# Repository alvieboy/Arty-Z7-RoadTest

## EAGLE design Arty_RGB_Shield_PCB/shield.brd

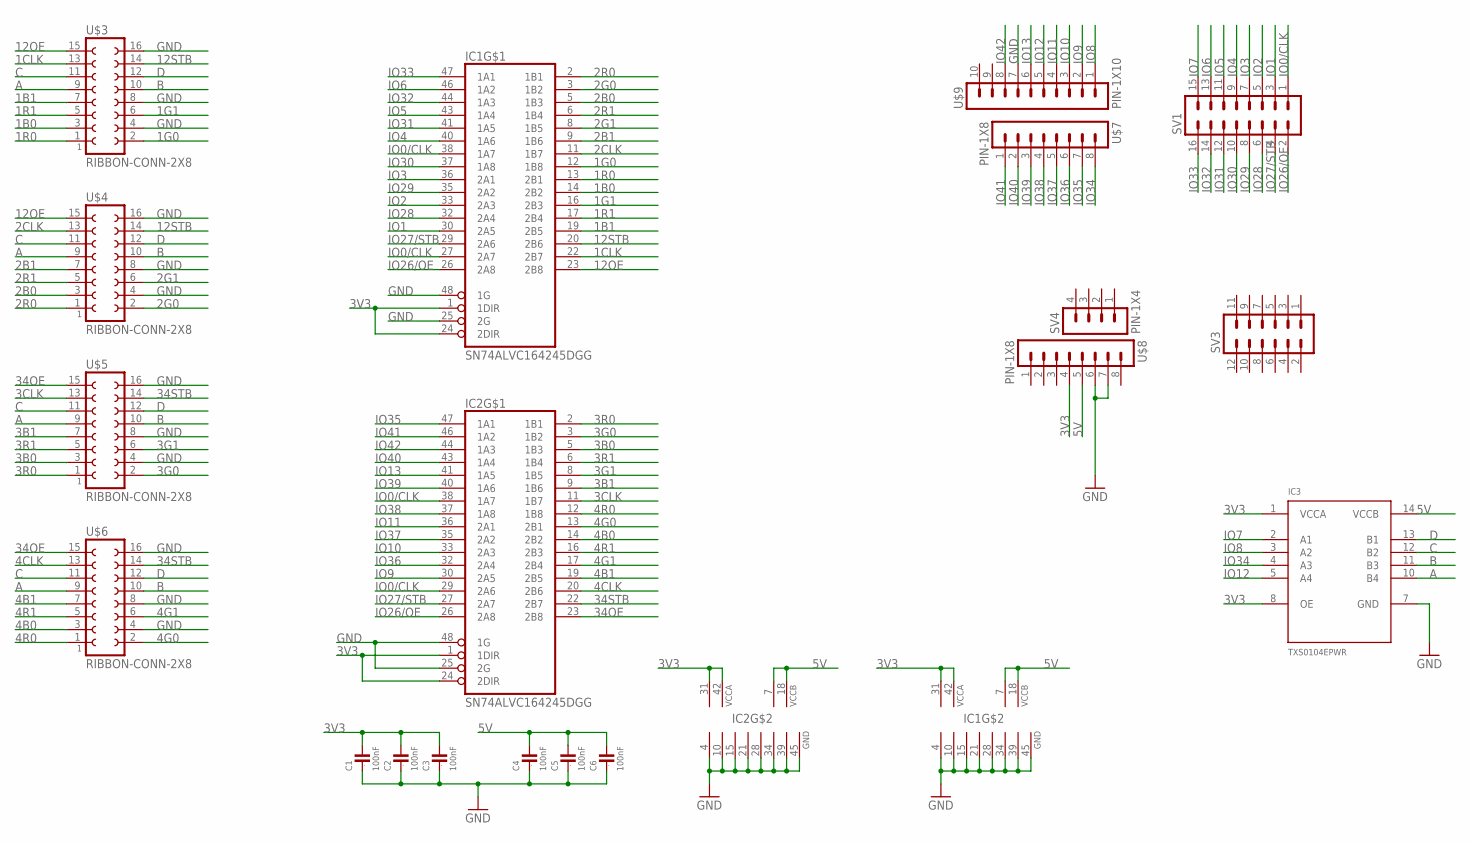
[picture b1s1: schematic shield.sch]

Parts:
C1, C2, C3, C4, C5, C6: 100nF; 0603
IC1, IC2: SN74ALVC164245DGG; TSSOP48
IC3: TXS0104EPWR; TSSOP14
SV1: MA08-2
SV3: MA06-2
SV4: PIN-1X4
U$3, U$4, U$5, U$6: RIBBON-CONN-2X8
U$7, U$8: PIN-1X8
U$9: PIN-1X10

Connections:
1B0: IC1.14 (2B2), U$3.3
1B1: IC1.19 (2B5), U$3.7
1CLK: IC1.22 (2B7), U$3.13
1G0: IC1.12 (1B8), U$3.2
1G1: IC1.16 (2B3), U$3.6
1R0: IC1.13 (2B1), U$3.1
1R1: IC1.17 (2B4), U$3.5
2B0: IC1.5 (1B3), U$4.3
2B1: IC1.9 (1B6), U$4.7
2CLK: IC1.11 (1B7), U$4.13
2G0: IC1.3 (1B2), U$4.2
2G1: IC1.8 (1B5), U$4.6
2R0: IC1.2 (1B1), U$4.1
2R1: IC1.6 (1B4), U$4.5
3B0: IC2.5 (1B3), U$5.3
3B1: IC2.9 (1B6), U$5.7
3CLK: IC2.11 (1B7), U$5.13
3G0: IC2.3 (1B2), U$5.2
3G1: IC2.8 (1B5), U$5.6
3R0: IC2.2 (1B1), U$5.1
3R1: IC2.6 (1B4), U$5.5
3V3: C1.2, C2.2, C3.2, IC1.1 (1DIR), IC1.24 (2DIR), IC1.31 (VCCA), IC1.42 (VCCA), IC2.1 (1DIR), IC2.24 (2DIR), IC2.31 (VCCA), IC2.42 (VCCA), IC3.1 (VCCA), IC3.8 (OE), U$8.4
4B0: IC2.14 (2B2), U$6.3
4B1: IC2.19 (2B5), U$6.7
4CLK: IC2.20 (2B6), U$6.13
4G0: IC2.13 (2B1), U$6.2
4G1: IC2.17 (2B4), U$6.6
4R0: IC2.12 (1B8), U$6.1
4R1: IC2.16 (2B3), U$6.5
5V: C4.2, C5.2, C6.2, IC1.7 (VCCB), IC1.18 (VCCB), IC2.7 (VCCB), IC2.18 (VCCB), IC3.14 (VCCB), U$8.5
12OE: IC1.23 (2B8), U$3.15, U$4.15
12STB: IC1.20 (2B6), U$3.14, U$4.14
34OE: IC2.23 (2B8), U$5.15, U$6.15
34STB: IC2.22 (2B7), U$5.14, U$6.14
A: IC3.10 (B4), U$3.9, U$4.9, U$5.9, U$6.9
B: IC3.11 (B3), U$3.10, U$4.10, U$5.10, U$6.10
C: IC3.12 (B2), U$3.11, U$4.11, U$5.11, U$6.11
D: IC3.13 (B1), U$3.12, U$4.12, U$5.12, U$6.12
GND: C1.1, C2.1, C3.1, C4.1, C5.1, C6.1, IC1.4 (GND), IC1.10 (GND), IC1.15 (GND), IC1.21 (GND), IC1.25 (2G), IC1.28 (GND), IC1.34 (GND), IC1.39 (GND), IC1.45 (GND), IC1.48 (1G), IC2.4 (GND), IC2.10 (GND), IC2.15 (GND), IC2.21 (GND), IC2.25 (2G), IC2.28 (GND), IC2.34 (GND), IC2.39 (GND), IC2.45 (GND), IC2.48 (1G), IC3.7 (GND), U$3.4, U$3.8, U$3.16, U$4.4, U$4.8, U$4.16, U$5.4, U$5.8, U$5.16, U$6.4, U$6.8, U$6.16, U$8.6, U$8.7, U$9.7
IO0/CLK: IC1.27 (2A7), IC1.38 (1A7), IC2.29 (2A6), IC2.38 (1A7), SV1.1
IO1: IC1.30 (2A5), SV1.3
IO2: IC1.33 (2A3), SV1.5
IO3: IC1.36 (2A1), SV1.7
IO4: IC1.40 (1A6), SV1.9
IO5: IC1.43 (1A4), SV1.11
IO6: IC1.46 (1A2), SV1.13
IO7: IC3.2 (A1), SV1.15
IO8: IC3.3 (A2), U$9.1
IO9: IC2.30 (2A5), U$9.2
IO10: IC2.33 (2A3), U$9.3
IO11: IC2.36 (2A1), U$9.4
IO12: IC3.5 (A4), U$9.5
IO13: IC2.41 (1A5), U$9.6
IO26/OE: IC1.26 (2A8), IC2.26 (2A8), SV1.2
IO27/STB: IC1.29 (2A6), IC2.27 (2A7), SV1.4
IO28: IC1.32 (2A4), SV1.6
IO29: IC1.35 (2A2), SV1.8
IO30: IC1.37 (1A8), SV1.10
IO31: IC1.41 (1A5), SV1.12
IO32: IC1.44 (1A3), SV1.14
IO33: IC1.47 (1A1), SV1.16
IO34: IC3.4 (A3), U$7.8
IO35: IC2.47 (1A1), U$7.7
IO36: IC2.32 (2A4), U$7.6
IO37: IC2.35 (2A2), U$7.5
IO38: IC2.37 (1A8), U$7.4
IO39: IC2.40 (1A6), U$7.3
IO40: IC2.43 (1A4), U$7.2
IO41: IC2.46 (1A2), U$7.1
IO42: IC2.44 (1A3), U$9.8

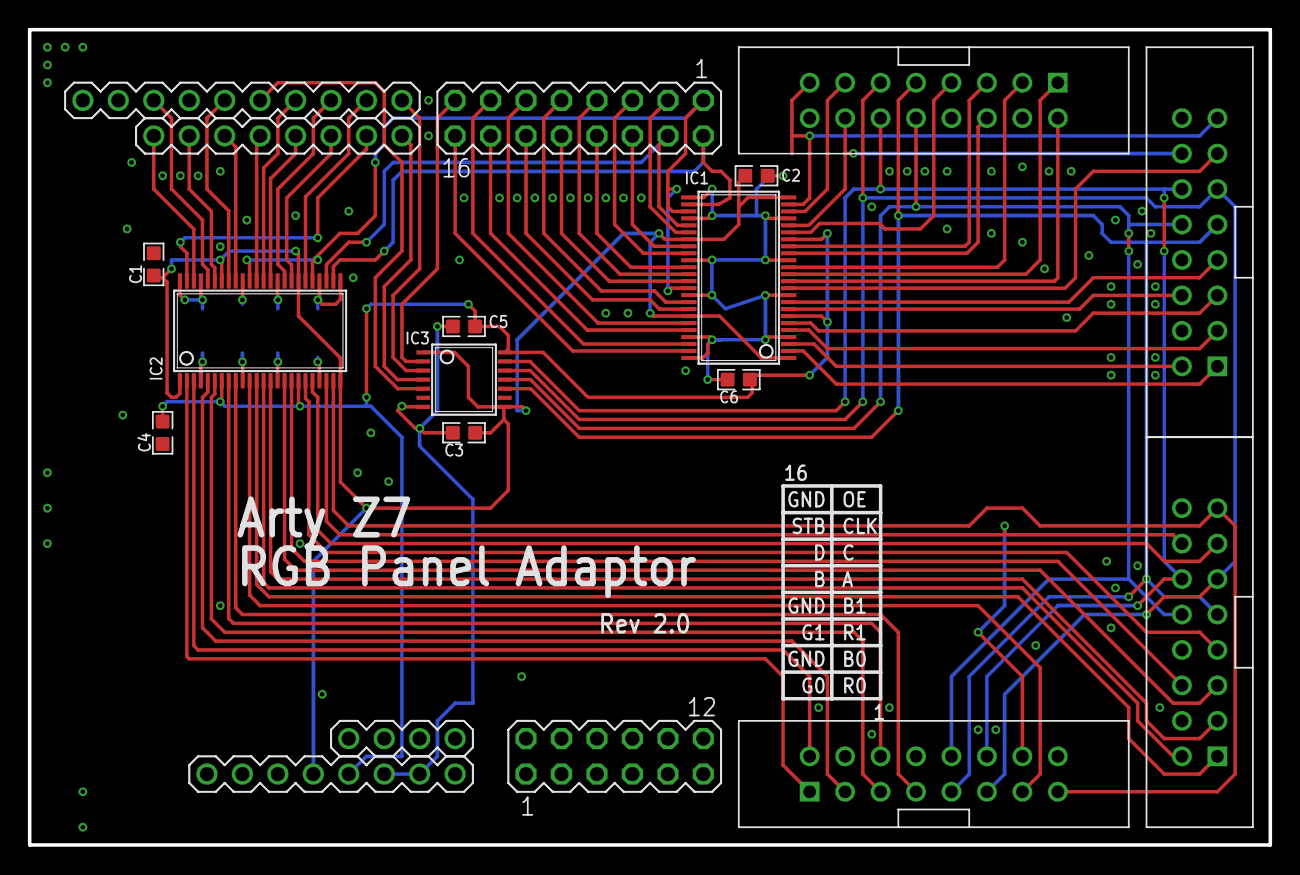
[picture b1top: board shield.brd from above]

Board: 2 copper layers, 88.9 x 58.4 mm, 19 parts (0 on the bottom side), 70 nets.

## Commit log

2018-08-22 add V1 board
2018-08-22 add V2 board
